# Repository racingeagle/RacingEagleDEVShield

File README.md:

# RacingEagleDEVShield
## Ein Arduino Shield für Anfänger und Schüler
Es dient als Adapter, der die Pins beschriftet und nach Funktionen sortiert heraus führt.
Es können alle Arduinos mit Nano-Formfaktor darauf gesteckt werden. Die USB-Buchse zeigt dabei in die entgegengesetzte Richtung der Anschlussklemme und befindet sich über dem "Racing Eagle DEV Shield"-Schriftzug.

__Bitte schließen Sie den Arduino nicht per USB an ihren PC an, solange eine Spannung an der DC-Klemme anliegt.__

Sollten Sie Fehler im Platinendesign finden melden sie diese bitte bei *Issues*.

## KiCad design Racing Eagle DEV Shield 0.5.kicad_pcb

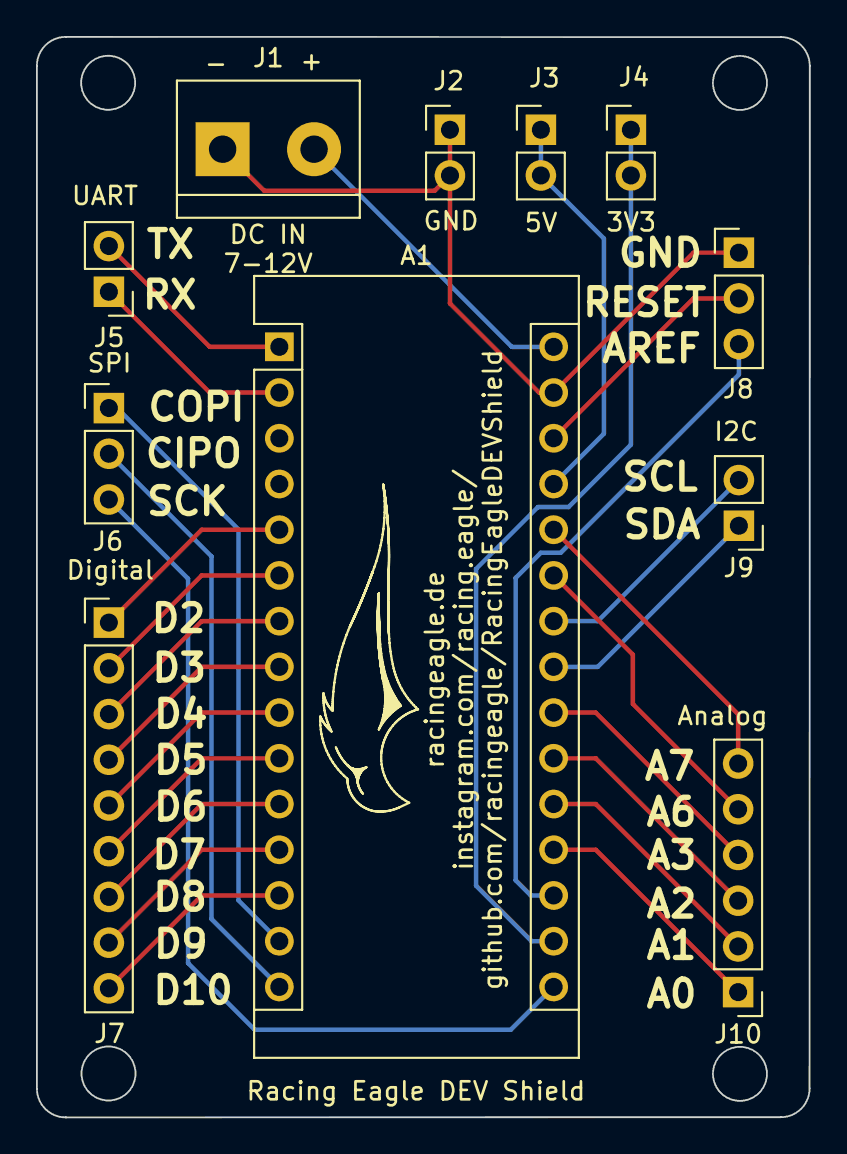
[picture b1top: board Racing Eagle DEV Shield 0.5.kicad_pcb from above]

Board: 2 copper layers, 42.9 x 60.0 mm, 11 parts (0 on the bottom side), 28 nets.

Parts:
A1: Arduino_Nano_v3.x; Arduino_Nano
J1: Screw_Terminal_01x02; TerminalBlock_bornier-2_P5.08mm
J2: Conn_GND; PinHeader_1x02_P2.54mm_Vertical
J3: Conn_+5V; PinHeader_1x02_P2.54mm_Vertical
J4: Conn_3V3; PinHeader_1x02_P2.54mm_Vertical
J5: Conn_UART; PinHeader_1x02_P2.54mm_Vertical
J6: Conn_SPI; PinHeader_1x03_P2.54mm_Vertical
J7: Conn_Digital; PinHeader_1x09_P2.54mm_Vertical
J8: Conn_AREF_RESET; PinHeader_1x03_P2.54mm_Vertical
J9: Conn_I2C; PinHeader_1x02_P2.54mm_Vertical
J10: Conn_Analog; PinHeader_1x06_P2.54mm_Vertical

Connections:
unnamed: A1.1 (D1/TX), J5.2
unnamed: A1.2 (D0/RX), J5.1
unnamed: A1.5 (D2), J7.1
unnamed: A1.6 (D3), J7.2
unnamed: A1.7 (D4), J7.3
unnamed: A1.8 (D5), J7.4
unnamed: A1.9 (D6), J7.5
unnamed: A1.10 (D7), J7.6
unnamed: A1.11 (D8), J7.7
unnamed: A1.12 (D9), J7.8
unnamed: A1.13 (D10), J7.9
unnamed: A1.14 (D11), J6.1
unnamed: A1.15 (D12), J6.2
unnamed: A1.16 (D13), J6.3
unnamed: A1.17 (3V3), J4.1, J4.2
unnamed: A1.18 (AREF), J8.3
unnamed: A1.19 (A0), J10.1
unnamed: A1.20 (A1), J10.2
unnamed: A1.21 (A2), J10.3
unnamed: A1.22 (A3), J10.4
unnamed: A1.23 (A4), J9.1
unnamed: A1.24 (A5), J9.2
unnamed: A1.25 (A6), J10.5
unnamed: A1.26 (A7), J10.6
unnamed: A1.27 (+5V), J3.1, J3.2
unnamed: A1.28 (~RESET), J8.2
unnamed: A1.29 (GND), J1.1, J2.1, J2.2, J8.1
unnamed: A1.30 (VIN), J1.2
